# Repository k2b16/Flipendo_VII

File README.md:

Step 4: Setting up Component Library

Note: If done according to the guide, the component library will be located in the Component_library folder.

To set up the component library, you first have to open KiCAD. Then in the upper menu bar, open Preferences -> Configure Paths... In there first press the + to add a new entry.

As the next step, open Preferences -> Manage Symbol Libraries... There, Press the button shown on the image below, marked by 1 and then in the folder selection window, select all of the files inside Component Library/Symbols directory.

After that, bunch of symbol entries should appear to the symbol library browser.

A very similar thing has to be done with Footprints, except instead of selecting files inside the Footprints directory you must choose all of the .pretty directories in there. Adding Footprint libraries is done in Preferences -> Manage Footprint Libraries...

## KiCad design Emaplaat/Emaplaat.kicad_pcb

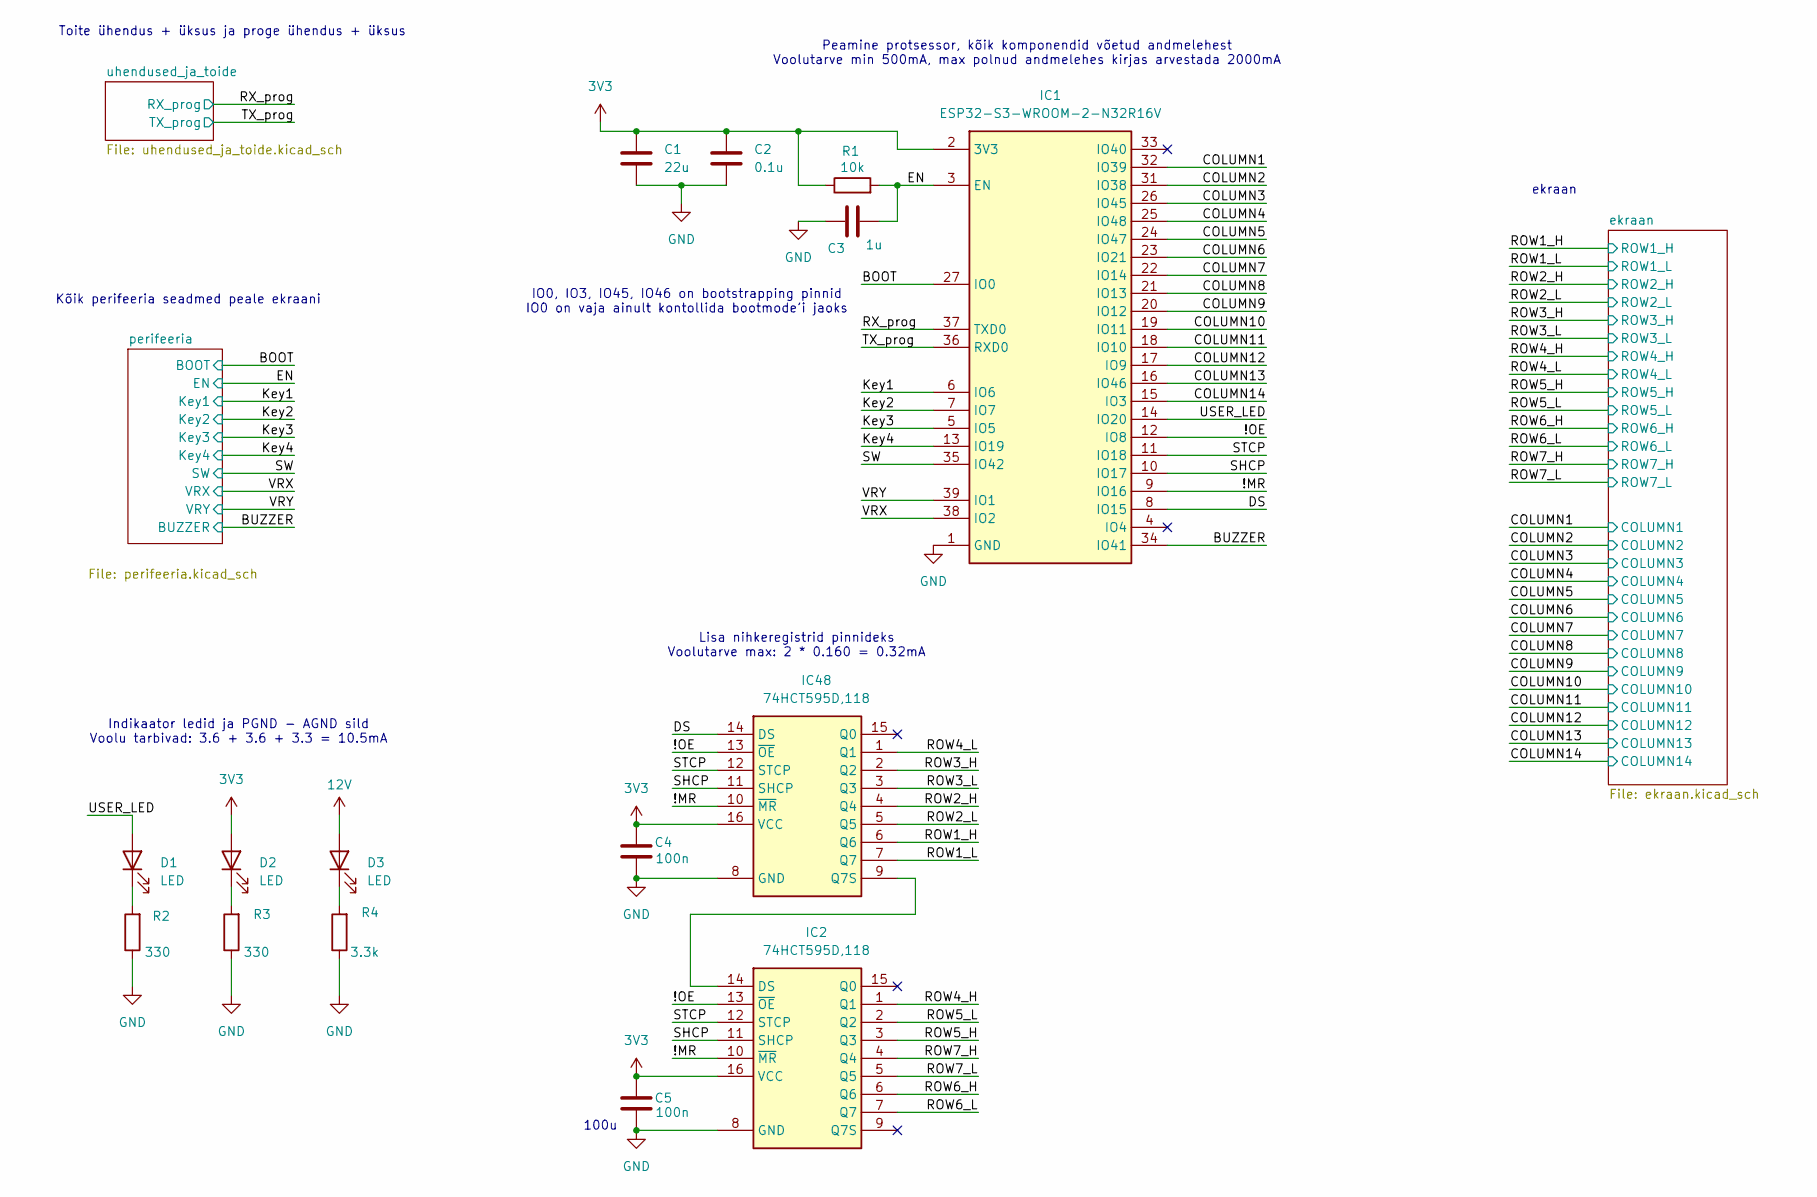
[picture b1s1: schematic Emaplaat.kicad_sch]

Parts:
C1: 22u; C_1206_3216Metric_Pad1.33x1.80mm_HandSolder
C2: 0.1u; C_0603_1608Metric_Pad1.08x0.95mm_HandSolder
C3: 1u; C_0603_1608Metric_Pad1.08x0.95mm_HandSolder
C4, C5: 100n; C_0603_1608Metric_Pad1.08x0.95mm_HandSolder
D1, D2, D3: LED; LED_0603_1608Metric_Pad1.05x0.95mm_HandSolder
IC1: ESP32-S3-WROOM-2-N32R16V; ESP32S3WROOM2N32R16V; Mouser Part Number 356-SP32S3WM2N32R16V
IC2, IC48: 74HCT595D,118; SOIC127P600X175-16N; Manufacturer_Part_Number 74HCT595D,118
R1: 10k; R_0603_1608Metric_Pad0.98x0.95mm_HandSolder
R2, R3: 330; R_0603_1608Metric_Pad0.98x0.95mm_HandSolder
R4: 3.3k; R_0603_1608Metric_Pad0.98x0.95mm_HandSolder

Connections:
3V3: C1.1, C2.1, C4.2, C5.2, D2.2 (A), IC1.2 (3V3), IC2.16 (VCC), IC48.16 (VCC), R1.1; also elsewhere on the board
12V: D3.2 (A); also elsewhere on the board
/!MR: IC1.9 (IO16), IC2.10 (~MR), IC48.10 (~MR)
/!OE: IC1.12 (IO8), IC2.13 (~OE), IC48.13 (~OE)
/BOOT: IC1.27 (IO0); also elsewhere on the board
/BUZZER: IC1.34 (IO41); also elsewhere on the board
/COLUMN1: IC1.32 (IO39); also elsewhere on the board
/COLUMN2: IC1.31 (IO38); also elsewhere on the board
/COLUMN3: IC1.26 (IO45); also elsewhere on the board
/COLUMN4: IC1.25 (IO48); also elsewhere on the board
/COLUMN5: IC1.24 (IO47); also elsewhere on the board
/COLUMN6: IC1.23 (IO21); also elsewhere on the board
/COLUMN7: IC1.22 (IO14); also elsewhere on the board
/COLUMN8: IC1.21 (IO13); also elsewhere on the board
/COLUMN9: IC1.20 (IO12); also elsewhere on the board
/COLUMN10: IC1.19 (IO11); also elsewhere on the board
/COLUMN11: IC1.18 (IO10); also elsewhere on the board
/COLUMN12: IC1.17 (IO9); also elsewhere on the board
/COLUMN13: IC1.16 (IO46); also elsewhere on the board
/COLUMN14: IC1.15 (IO3); also elsewhere on the board
/DS: IC1.8 (IO15), IC48.14 (DS)
/EN: C3.2, IC1.3 (EN), R1.2; also elsewhere on the board
/Key1: IC1.6 (IO6); also elsewhere on the board
/Key2: IC1.7 (IO7); also elsewhere on the board
/Key3: IC1.5 (IO5); also elsewhere on the board
/Key4: IC1.13 (IO19); also elsewhere on the board
/ROW1_H: IC48.6 (Q6); also elsewhere on the board
/ROW1_L: IC48.7 (Q7); also elsewhere on the board
/ROW2_H: IC48.4 (Q4); also elsewhere on the board
/ROW2_L: IC48.5 (Q5); also elsewhere on the board
/ROW3_H: IC48.2 (Q2); also elsewhere on the board
/ROW3_L: IC48.3 (Q3); also elsewhere on the board
/ROW4_H: IC2.1 (Q1); also elsewhere on the board
/ROW4_L: IC48.1 (Q1); also elsewhere on the board
/ROW5_H: IC2.3 (Q3); also elsewhere on the board
/ROW5_L: IC2.2 (Q2); also elsewhere on the board
/ROW6_H: IC2.6 (Q6); also elsewhere on the board
/ROW6_L: IC2.7 (Q7); also elsewhere on the board
/ROW7_H: IC2.4 (Q4); also elsewhere on the board
/ROW7_L: IC2.5 (Q5); also elsewhere on the board
/RX_prog: IC1.37 (TXD0); also elsewhere on the board
/SHCP: IC1.10 (IO17), IC2.11 (SHCP), IC48.11 (SHCP)
/STCP: IC1.11 (IO18), IC2.12 (STCP), IC48.12 (STCP)
/SW: IC1.35 (IO42); also elsewhere on the board
/TX_prog: IC1.36 (RXD0); also elsewhere on the board
/USER_LED: D1.2 (A), IC1.14 (IO20)
/VRX: IC1.38 (IO2); also elsewhere on the board
/VRY: IC1.39 (IO1); also elsewhere on the board
GND: C1.2, C2.2, C3.1, C4.1, C5.1, IC1.1 (GND), IC1.40 (GND), IC1.41 (GND), IC1.42 (GND), IC1.43 (GND), IC1.44 (GND), IC1.45 (GND), IC1.46 (GND), IC1.47 (GND), IC1.48 (GND), IC1.49 (GND), IC2.8 (GND), IC48.8 (GND), R2.1, R3.1, R4.1; also elsewhere on the board
unnamed: D1.1 (K), R2.2
unnamed: D2.1 (K), R3.2
unnamed: D3.1 (K), R4.2
unnamed: IC2.14 (DS), IC48.9 (Q7S)

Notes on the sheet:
Toite ühendus + üksus ja proge ühendus + üksus
Kõik perifeeria seadmed peale ekraani
Indikaator ledid ja PGND - AGND sild Voolu tarbivad: 3.6 + 3.6 + 3.3 = 10.5mA
Peamine protsessor, kõik komponendid võetud andmelehest Voolutarve min 500mA, max polnud andmelehes kirjas arvestada 2000mA
IO0, IO3, IO45, IO46 on bootstrapping pinnid IO0 on vaja ainult kontollida bootmode'i jaoks
ekraan
Lisa nihkeregistrid pinnideks Voolutarve max: 2 * 0.160 = 0.32mA
100u

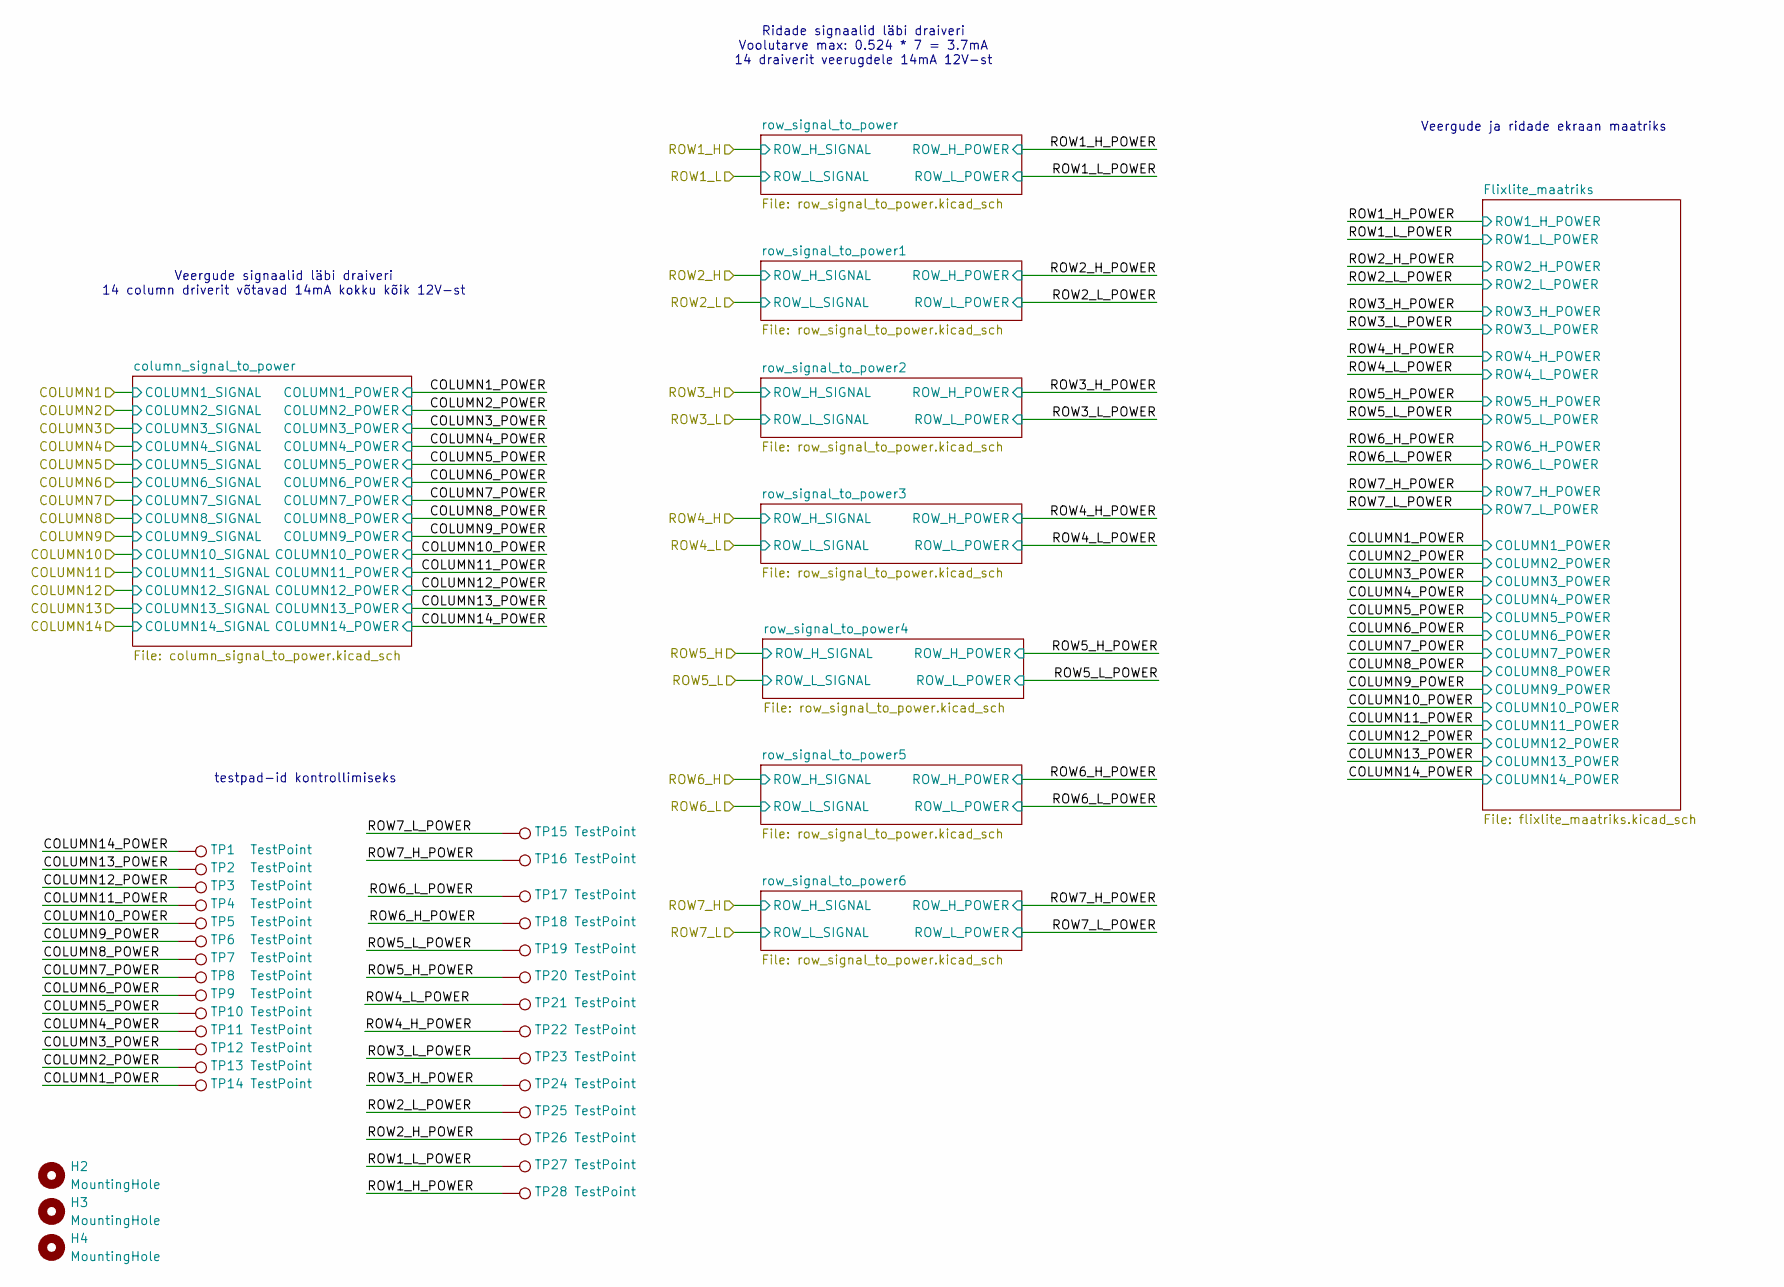
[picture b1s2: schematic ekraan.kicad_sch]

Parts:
H2, H3, H4: MountingHole; MountingHole_3mm_Pad
TP1, TP2, TP3, TP4, TP5, TP6, TP7, TP8, TP9, TP10, TP11, TP12, TP13, TP14, TP15, TP16, TP17, TP18, TP19, TP20, TP21, TP22, TP23, TP24, TP25, TP26, TP27, TP28: TestPoint; TestPoint_Pad_D1.0mm

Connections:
/ekraan/COLUMN1_POWER: TP14.1; also elsewhere on the board
/ekraan/COLUMN2_POWER: TP13.1; also elsewhere on the board
/ekraan/COLUMN3_POWER: TP12.1; also elsewhere on the board
/ekraan/COLUMN4_POWER: TP11.1; also elsewhere on the board
/ekraan/COLUMN5_POWER: TP10.1; also elsewhere on the board
/ekraan/COLUMN6_POWER: TP9.1; also elsewhere on the board
/ekraan/COLUMN7_POWER: TP8.1; also elsewhere on the board
/ekraan/COLUMN8_POWER: TP7.1; also elsewhere on the board
/ekraan/COLUMN9_POWER: TP6.1; also elsewhere on the board
/ekraan/COLUMN10_POWER: TP5.1; also elsewhere on the board
/ekraan/COLUMN11_POWER: TP4.1; also elsewhere on the board
/ekraan/COLUMN12_POWER: TP3.1; also elsewhere on the board
/ekraan/COLUMN13_POWER: TP2.1; also elsewhere on the board
/ekraan/COLUMN14_POWER: TP1.1; also elsewhere on the board
/ekraan/ROW1_H_POWER: TP28.1; also elsewhere on the board
/ekraan/ROW1_L_POWER: TP27.1; also elsewhere on the board
/ekraan/ROW2_H_POWER: TP26.1; also elsewhere on the board
/ekraan/ROW2_L_POWER: TP25.1; also elsewhere on the board
/ekraan/ROW3_H_POWER: TP24.1; also elsewhere on the board
/ekraan/ROW3_L_POWER: TP23.1; also elsewhere on the board
/ekraan/ROW4_H_POWER: TP22.1; also elsewhere on the board
/ekraan/ROW4_L_POWER: TP21.1; also elsewhere on the board
/ekraan/ROW5_H_POWER: TP20.1; also elsewhere on the board
/ekraan/ROW5_L_POWER: TP19.1; also elsewhere on the board
/ekraan/ROW6_H_POWER: TP18.1; also elsewhere on the board
/ekraan/ROW6_L_POWER: TP17.1; also elsewhere on the board
/ekraan/ROW7_H_POWER: TP16.1; also elsewhere on the board
/ekraan/ROW7_L_POWER: TP15.1; also elsewhere on the board

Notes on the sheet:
Veergude ja ridade ekraan maatriks
Veergude signaalid läbi draiveri 14 column driverit võtavad 14mA kokku kõik 12V-st
Ridade signaalid läbi draiveri Voolutarve max: 0.524 * 7 = 3.7mA 14 draiverit veerugdele 14mA 12V-st
testpad-id kontrollimiseks

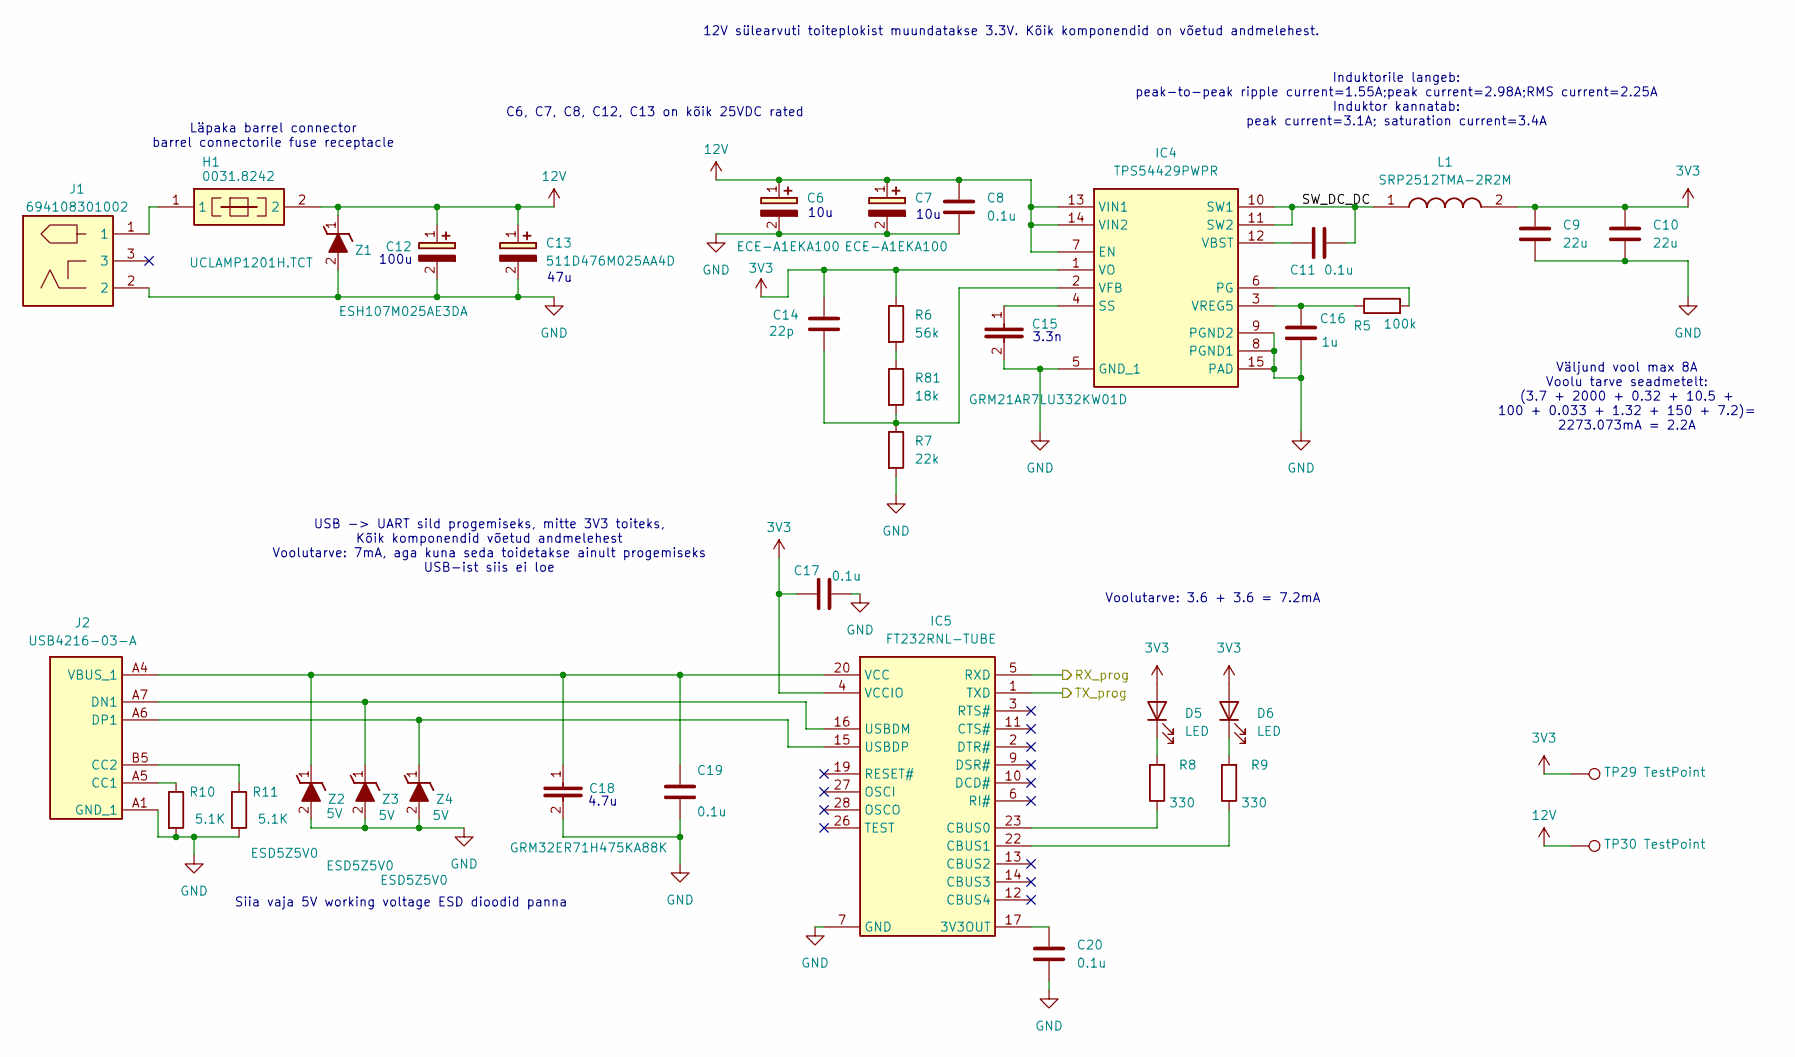
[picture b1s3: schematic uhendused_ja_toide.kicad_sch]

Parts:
C6, C7: ECE-A1EKA100; CAPPRD150W50D400H800; Mouser Part Number 667-ECE-A1EKA100
C8, C11, C17, C19, C20: 0.1u; C_0603_1608Metric_Pad1.08x0.95mm_HandSolder
C9, C10: 22u; C_1206_3216Metric_Pad1.33x1.80mm_HandSolder
C12: ESH107M025AE3DA; CAPPRD250W50D630H1250; Mouser Part Number 80-ESH107M025AE3DA
C13: 511D476M025AA4D; Mouser Part Number 75-511D476M025AA4D
C14: 22p; C_0603_1608Metric_Pad1.08x0.95mm_HandSolder
C15: GRM21AR7LU332KW01D; CAPC2012X130N; Manufacturer_Part_Number GRM21AR7LU332KW01D
C16: 1u; C_0603_1608Metric_Pad1.08x0.95mm_HandSolder
C18: GRM32ER71H475KA88K; CAPC3225X270N; Mouser Part Number 81-GRM32ER71H475KA8K
D5, D6: LED; LED_0603_1608Metric_Pad1.05x0.95mm_HandSolder
H1: 0031.8242; 00318242; Mouser Part Number N/A
IC4: TPS54429PWPR; Texas_HTSSOP-14-1EP_4.4x5mm_P0.65mm_EP3.4x5mm_Mask3.155x3.2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; Mouser Part Number 595-TPS54429PWPR
IC5: FT232RNL-TUBE; SOP65P780X200-28N; Mouser Part Number 895-FT232RNL-TUBE
J1: 694108301002; Manufacturer_Part_Number 694108301002
J2: USB4216-03-A; USB421603A; Manufacturer_Part_Number USB4216-03-A
L1: SRP2512TMA-2R2M; SRP2512TMA2R2M; Mouser Part Number 652-SRP2512TMA-2R2M
R5: 100k; R_0603_1608Metric_Pad0.98x0.95mm_HandSolder
R6: 56k; R_0603_1608Metric_Pad0.98x0.95mm_HandSolder
R7: 22k; R_0603_1608Metric_Pad0.98x0.95mm_HandSolder
R8, R9: 330; R_0603_1608Metric_Pad0.98x0.95mm_HandSolder
R10, R11: 5.1K; R_0603_1608Metric_Pad0.98x0.95mm_HandSolder
R81: 18k; R_0603_1608Metric_Pad0.98x0.95mm_HandSolder
TP29, TP30: TestPoint; TestPoint_Pad_D1.0mm
Z1: UCLAMP1201H.TCT; SODFL1608X70N; Mouser Part Number 947-UCLAMP1201H.TCT
Z2, Z3, Z4: ESD5Z5V0; D_SOD-523; Working voltage 5V

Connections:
3V3: C9.1, C10.1, C14.1, C17.1, D5.2 (A), D6.2 (A), IC4.1 (VO), IC5.4 (VCCIO), L1.2, R6.1, TP29.1; also elsewhere on the board
12V: C6.1 (+), C7.1 (+), C8.1, C12.1 (+), C13.1 (+), H1.2, IC4.7 (EN), IC4.13 (VIN1), IC4.14 (VIN2), TP30.1, Z1.1 (K); also elsewhere on the board
/RX_prog: IC5.5 (RXD); also elsewhere on the board
/TX_prog: IC5.1 (TXD); also elsewhere on the board
/uhendused_ja_toide/SW_DC_DC: C11.2, IC4.10 (SW1), IC4.11 (SW2), L1.1
GND: C6.2 (-), C7.2 (-), C8.2, C9.2, C10.2, C12.2 (-), C13.2 (-), C15.2, C16.2, C17.2, C18.2, C19.2, C20.2, IC4.5 (GND_1), IC4.8 (PGND1), IC4.9 (PGND2), IC4.15 (PAD), IC5.7 (GND), IC5.18 (GND_2), IC5.21 (GND_3), IC5.25 (AGND), J1.2, J2.A1 (GND_1), J2.B1 (GND_2), J2.G1 (GND_3), J2.G2 (GND_4), J2.G3 (GND_5), J2.G4 (GND_6), R7.2, R10.2, R11.2, Z1.2 (A), Z2.2 (A), Z3.2 (A), Z4.2 (A); also elsewhere on the board
unnamed: D5.1 (K), R8.2
unnamed: D6.1 (K), R9.2
unnamed: H1.1, J1.1
unnamed: IC4.6 (PG), R5.2
unnamed: C15.1, IC4.4 (SS)
unnamed: C11.1, IC4.12 (VBST)
unnamed: C14.2, IC4.2 (VFB), R7.1, R81.2
unnamed: C16.1, IC4.3 (VREG5), R5.1
unnamed: C20.1, IC5.17 (3V3OUT)
unnamed: IC5.23 (CBUS0), R8.1
unnamed: IC5.22 (CBUS1), R9.1
unnamed: IC5.16 (USBDM), J2.A7 (DN1), J2.B7 (DN2), Z3.1 (K)
unnamed: IC5.15 (USBDP), J2.A6 (DP1), J2.B6 (DP2), Z4.1 (K)
unnamed: C18.1, C19.1, IC5.20 (VCC), J2.A4 (VBUS_1), J2.B4 (VBUS_2), Z2.1 (K)
unnamed: J2.A5 (CC1), R10.1
unnamed: J2.B5 (CC2), R11.1
unnamed: J2.A8 (SBU1), J2.B8 (SBU2)
unnamed: R6.2, R81.1

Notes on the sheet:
12V sülearvuti toiteplokist muundatakse 3.3V. Kõik komponendid on võetud andmelehest.
C6, C7, C8, C12, C13 on kõik 25VDC rated
47u
10u
Siia vaja 5V working voltage ESD dioodid panna
Väljund vool max 8A Voolu tarve seadmetelt: (3.7 + 2000 + 0.32 + 10.5 + 100 + 0.033 + 1.32 + 150 + 7.2)= 2273.073mA = 2.2A
USB -> UART sild progemiseks, mitte 3V3 toiteks, Kõik komponendid võetud andmelehest Voolutarve: 7mA, aga kuna seda toidetakse ainult progemiseks USB-ist siis ei loe
4.7u
100u
Induktorile langeb: peak-to-peak ripple current=1.55A;peak current=2.98A;RMS current=2.25A Induktor kannatab: peak current=3.1A; saturation current=3.4A
3.3n
Läpaka barrel connector barrel connectorile fuse receptacle
Voolutarve: 3.6 + 3.6 = 7.2mA

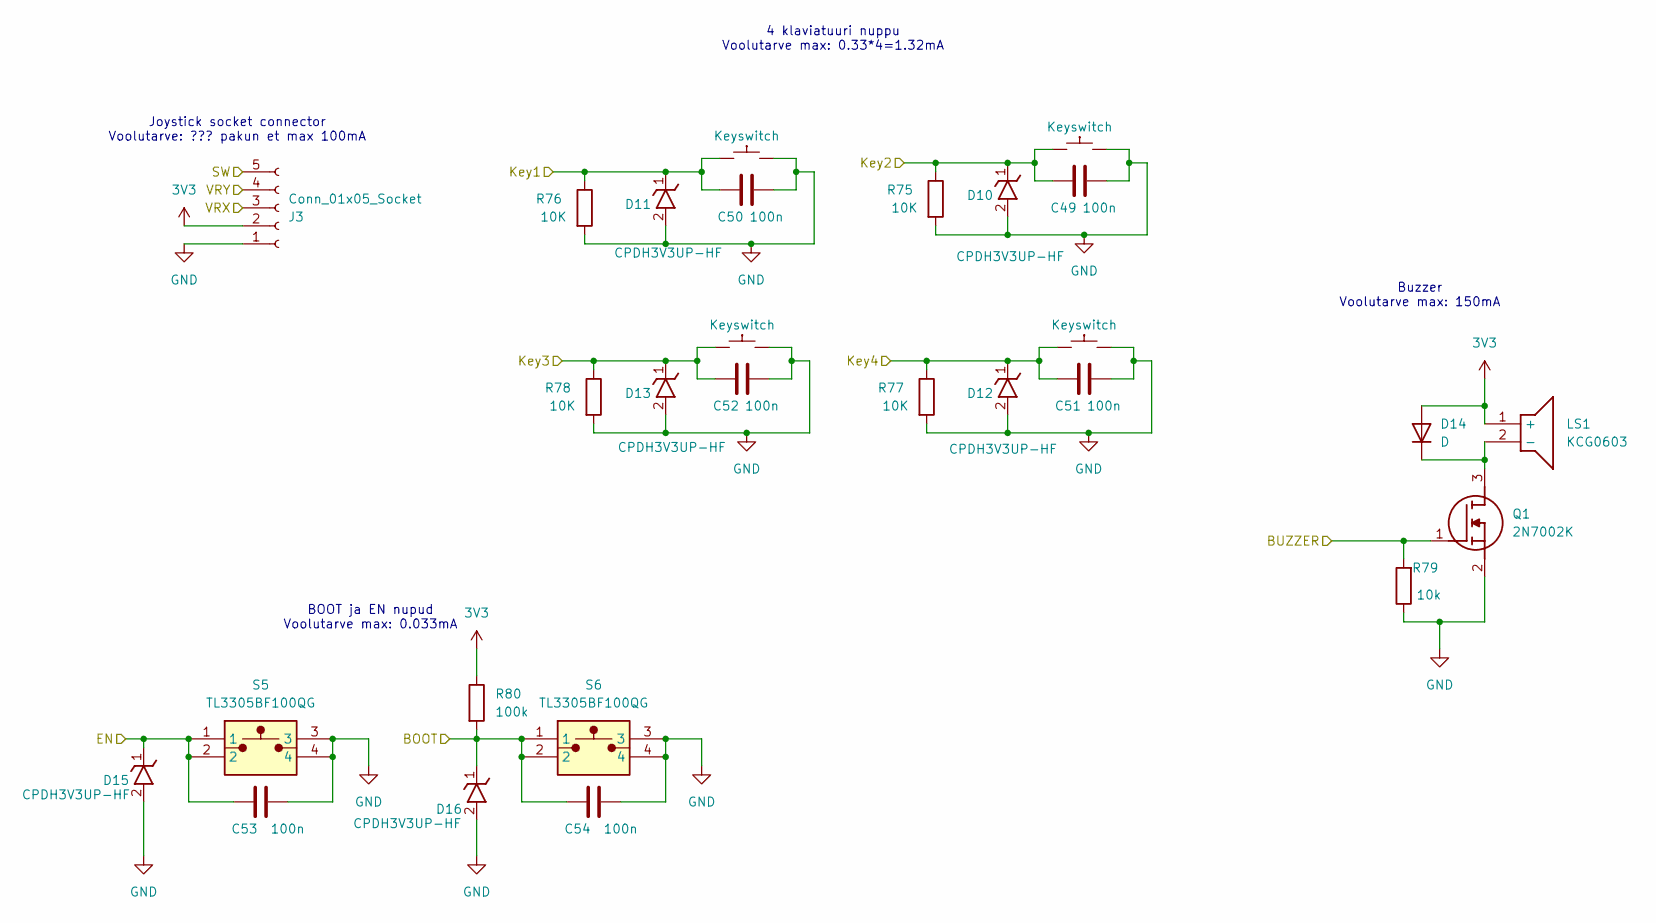
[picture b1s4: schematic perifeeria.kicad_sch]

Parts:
C49, C50, C51, C52, C53, C54: 100n; C_0603_1608Metric_Pad1.08x0.95mm_HandSolder
D10, D11, D12, D13, D15, D16: CPDH3V3UP-HF; D_SOD-523; Mouser Part Number 750-CPDH3V3UP-HF
D14: D; SOD-123FL
J3: Conn_01x05_Socket; PinSocket_1x05_P2.54mm_Horizontal
LS1: KCG0603; Manufacturer_Part_Number KCG0603
Q1: 2N7002K; SOT95P240X120-3N; Mouser Part Number 512-2N7002K
R75, R76, R77, R78: 10K; R_0603_1608Metric_Pad0.98x0.95mm_HandSolder
R79: 10k; R_0603_1608Metric_Pad0.98x0.95mm_HandSolder
R80: 100k; R_0603_1608Metric_Pad0.98x0.95mm_HandSolder
S1, S2, S3, S4: Keyswitch; SW_Cherry_MX_1.00u_PCB
S5, S6: TL3305BF100QG; TL3305BF160QG; Mouser Part Number 612-TL3305BF100QG

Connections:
3V3: D14.2 (A), J3.2, LS1.1 (+), R80.1; also elsewhere on the board
/BOOT: C54.1, D16.1 (K), R80.2, S6.1, S6.2; also elsewhere on the board
/BUZZER: Q1.1 (G), R79.2; also elsewhere on the board
/EN: C53.1, D15.1 (K), S5.1, S5.2; also elsewhere on the board
/Key1: C50.1, D11.1 (K), R76.1, S2.1; also elsewhere on the board
/Key2: C49.1, D10.1 (K), R75.1, S1.1; also elsewhere on the board
/Key3: C52.1, D13.1 (K), R78.1, S4.1; also elsewhere on the board
/Key4: C51.1, D12.1 (K), R77.1, S3.1; also elsewhere on the board
/SW: J3.5; also elsewhere on the board
/VRX: J3.3; also elsewhere on the board
/VRY: J3.4; also elsewhere on the board
GND: C49.2, C50.2, C51.2, C52.2, C53.2, C54.2, D10.2 (A), D11.2 (A), D12.2 (A), D13.2 (A), D15.2 (A), D16.2 (A), J3.1, Q1.2 (S), R75.2, R76.2, R77.2, R78.2, R79.1, S1.2, S2.2, S3.2, S4.2, S5.3, S5.4, S6.3, S6.4; also elsewhere on the board
unnamed: D14.1 (K), LS1.2 (-), Q1.3 (D)

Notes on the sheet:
Buzzer Voolutarve max: 150mA
4 klaviatuuri nuppu Voolutarve max: 0.33*4=1.32mA
Joystick socket connector Voolutarve: ??? pakun et max 100mA
BOOT ja EN nupud Voolutarve max: 0.033mA

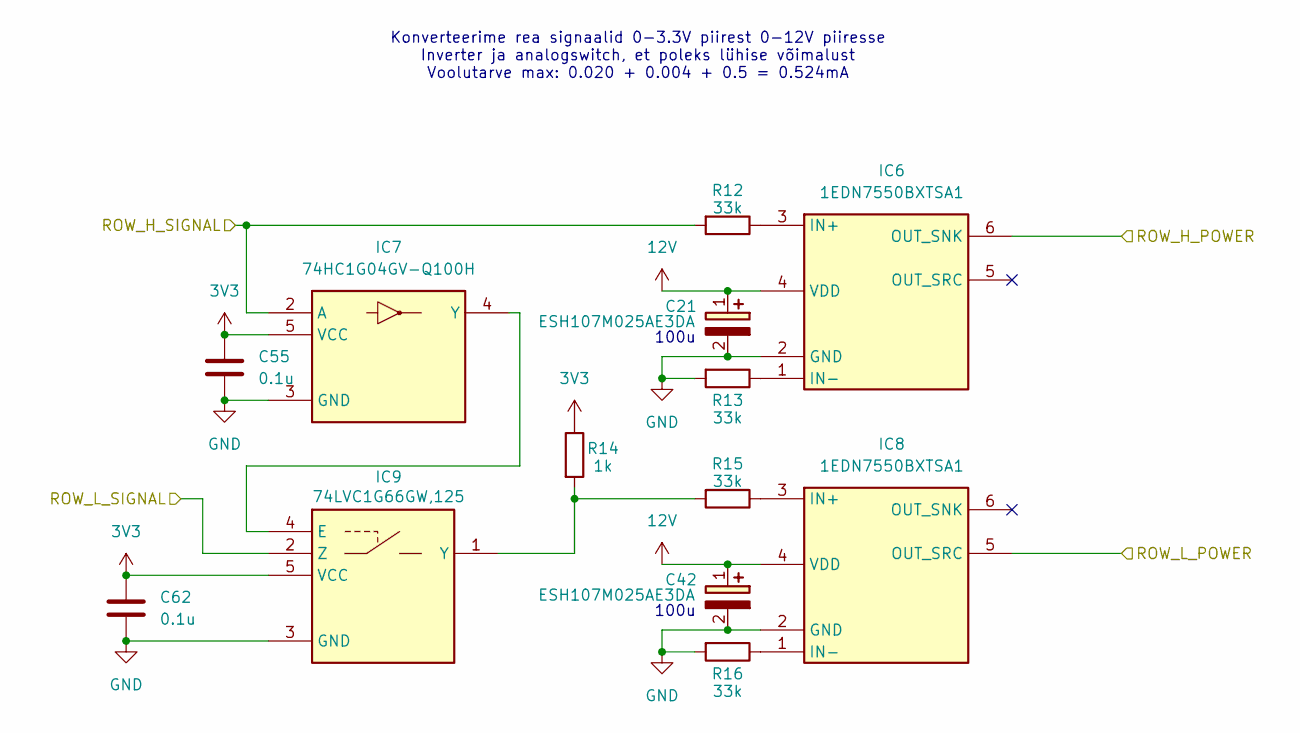
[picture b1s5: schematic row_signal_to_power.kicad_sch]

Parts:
C21, C42: ESH107M025AE3DA; CAPPRD250W50D630H1250; Mouser Part Number 80-ESH107M025AE3DA
C55, C62: 0.1u; C_0603_1608Metric_Pad1.08x0.95mm_HandSolder
IC6, IC8: 1EDN7550BXTSA1; SOT95P280X145-6N; Mouser Part Number 726-1EDN7550BXTSA1
IC7: 74HC1G04GV-Q100H; SOT95P275X110-5N; Mouser Part Number 771-74HC1G04GV-Q100H
IC9: 74LVC1G66GW,125; SOT65P212X110-5N; Mouser Part Number 771-74LVC1G66GW-G
R12, R13, R15, R16: 33k; R_0603_1608Metric_Pad0.98x0.95mm_HandSolder
R14: 1k; R_0603_1608Metric_Pad0.98x0.95mm_HandSolder

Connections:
3V3: C55.1, C62.1, IC7.5 (VCC), IC9.5 (VCC), R14.1; also elsewhere on the board
12V: C21.1 (+), C42.1 (+), IC6.4 (VDD), IC8.4 (VDD); also elsewhere on the board
/ROW2_H: IC7.2 (A), R12.2; also elsewhere on the board
/ROW2_L: IC9.2 (Z); also elsewhere on the board
/ekraan/ROW2_H_POWER: IC6.6 (OUT_SNK); also elsewhere on the board
/ekraan/ROW2_L_POWER: IC8.5 (OUT_SRC); also elsewhere on the board
GND: C21.2 (-), C42.2 (-), C55.2, C62.2, IC6.2 (GND), IC7.3 (GND), IC8.2 (GND), IC9.3 (GND), R13.2, R16.2; also elsewhere on the board
unnamed: IC6.3 (IN+), R12.1
unnamed: IC6.1 (IN-), R13.1
unnamed: IC7.4 (Y), IC9.4 (E)
unnamed: IC8.3 (IN+), R15.1
unnamed: IC8.1 (IN-), R16.1
unnamed: IC9.1 (Y), R14.2, R15.2

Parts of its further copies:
C22, C23, C24, C25, C26, C41, C43, C44, C45, C46, C47, C48: ESH107M025AE3DA; CAPPRD250W50D630H1250; Mouser Part Number 80-ESH107M025AE3DA
C56, C57, C58, C59, C60, C61, C63, C64, C65, C66, C67, C68: 0.1u; C_0603_1608Metric_Pad1.08x0.95mm_HandSolder
IC10, IC12, IC14, IC16, IC32, IC34, IC36, IC38, IC40, IC42, IC44, IC46: 1EDN7550BXTSA1; SOT95P280X145-6N; Mouser Part Number 726-1EDN7550BXTSA1
IC11, IC15, IC33, IC37, IC41, IC45: 74HC1G04GV-Q100H; SOT95P275X110-5N; Mouser Part Number 771-74HC1G04GV-Q100H
IC13, IC17, IC35, IC39, IC43, IC47: 74LVC1G66GW,125; SOT65P212X110-5N; Mouser Part Number 771-74LVC1G66GW-G
R17, R18, R20, R21, R22, R23, R25, R26, R55, R56, R58, R59, R60, R61, R63, R64, R65, R66, R68, R69, R70, R71, R73, R74: 33k; R_0603_1608Metric_Pad0.98x0.95mm_HandSolder
R19, R24, R57, R62, R67, R72: 1k; R_0603_1608Metric_Pad0.98x0.95mm_HandSolder

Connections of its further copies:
3V3: C56.1, C57.1, C58.1, C59.1, C60.1, C61.1, C63.1, C64.1, C65.1, C66.1, C67.1, C68.1, IC11.5 (VCC), IC13.5 (VCC), IC15.5 (VCC), IC17.5 (VCC), IC33.5 (VCC), IC35.5 (VCC), IC37.5 (VCC), IC39.5 (VCC), IC41.5 (VCC), IC43.5 (VCC), IC45.5 (VCC), IC47.5 (VCC), R19.1, R24.1, R57.1, R62.1, R67.1, R72.1; also elsewhere on the board
12V: C22.1 (+), C23.1 (+), C24.1 (+), C25.1 (+), C26.1 (+), C41.1 (+), C43.1 (+), C44.1 (+), C45.1 (+), C46.1 (+), C47.1 (+), C48.1 (+), IC10.4 (VDD), IC12.4 (VDD), IC14.4 (VDD), IC16.4 (VDD), IC32.4 (VDD), IC34.4 (VDD), IC36.4 (VDD), IC38.4 (VDD), IC40.4 (VDD), IC42.4 (VDD), IC44.4 (VDD), IC46.4 (VDD); also elsewhere on the board
/ROW1_H: IC15.2 (A), R22.2; also elsewhere on the board
/ROW1_L: IC17.2 (Z); also elsewhere on the board
/ROW3_H: IC11.2 (A), R17.2; also elsewhere on the board
/ROW3_L: IC13.2 (Z); also elsewhere on the board
/ROW4_H: IC33.2 (A), R55.2; also elsewhere on the board
/ROW4_L: IC35.2 (Z); also elsewhere on the board
/ROW5_H: IC37.2 (A), R60.2; also elsewhere on the board
/ROW5_L: IC39.2 (Z); also elsewhere on the board
/ROW6_H: IC41.2 (A), R65.2; also elsewhere on the board
/ROW6_L: IC43.2 (Z); also elsewhere on the board
/ROW7_H: IC45.2 (A), R70.2; also elsewhere on the board
/ROW7_L: IC47.2 (Z); also elsewhere on the board
/ekraan/ROW1_H_POWER: IC14.6 (OUT_SNK); also elsewhere on the board
/ekraan/ROW1_L_POWER: IC16.5 (OUT_SRC); also elsewhere on the board
/ekraan/ROW3_H_POWER: IC10.6 (OUT_SNK); also elsewhere on the board
/ekraan/ROW3_L_POWER: IC12.5 (OUT_SRC); also elsewhere on the board
/ekraan/ROW4_H_POWER: IC32.6 (OUT_SNK); also elsewhere on the board
/ekraan/ROW4_L_POWER: IC34.5 (OUT_SRC); also elsewhere on the board
/ekraan/ROW5_H_POWER: IC36.6 (OUT_SNK); also elsewhere on the board
/ekraan/ROW5_L_POWER: IC38.5 (OUT_SRC); also elsewhere on the board
/ekraan/ROW6_H_POWER: IC40.6 (OUT_SNK); also elsewhere on the board
/ekraan/ROW6_L_POWER: IC42.5 (OUT_SRC); also elsewhere on the board
/ekraan/ROW7_H_POWER: IC44.6 (OUT_SNK); also elsewhere on the board
/ekraan/ROW7_L_POWER: IC46.5 (OUT_SRC); also elsewhere on the board
GND: C22.2 (-), C23.2 (-), C24.2 (-), C25.2 (-), C26.2 (-), C41.2 (-), C43.2 (-), C44.2 (-), C45.2 (-), C46.2 (-), C47.2 (-), C48.2 (-), C56.2, C57.2, C58.2, C59.2, C60.2, C61.2, C63.2, C64.2, C65.2, C66.2, C67.2, C68.2, IC10.2 (GND), IC11.3 (GND), IC12.2 (GND), IC13.3 (GND), IC14.2 (GND), IC15.3 (GND), IC16.2 (GND), IC17.3 (GND), IC32.2 (GND), IC33.3 (GND), IC34.2 (GND), IC35.3 (GND), IC36.2 (GND), IC37.3 (GND), IC38.2 (GND), IC39.3 (GND), IC40.2 (GND), IC41.3 (GND), IC42.2 (GND), IC43.3 (GND), IC44.2 (GND), IC45.3 (GND), IC46.2 (GND), IC47.3 (GND), R18.2, R21.2, R23.2, R26.2, R56.2, R59.2, R61.2, R64.2, R66.2, R69.2, R71.2, R74.2; also elsewhere on the board
unnamed: IC10.3 (IN+), R17.1
unnamed: IC10.1 (IN-), R18.1
unnamed: IC11.4 (Y), IC13.4 (E)
unnamed: IC12.3 (IN+), R20.1
unnamed: IC12.1 (IN-), R21.1
unnamed: IC13.1 (Y), R19.2, R20.2
unnamed: IC14.3 (IN+), R22.1
unnamed: IC14.1 (IN-), R23.1
unnamed: IC15.4 (Y), IC17.4 (E)
unnamed: IC16.3 (IN+), R25.1
unnamed: IC16.1 (IN-), R26.1
unnamed: IC17.1 (Y), R24.2, R25.2
unnamed: IC32.3 (IN+), R55.1
unnamed: IC32.1 (IN-), R56.1
unnamed: IC33.4 (Y), IC35.4 (E)
unnamed: IC34.3 (IN+), R58.1
unnamed: IC34.1 (IN-), R59.1
unnamed: IC35.1 (Y), R57.2, R58.2
unnamed: IC36.3 (IN+), R60.1
unnamed: IC36.1 (IN-), R61.1
unnamed: IC37.4 (Y), IC39.4 (E)
unnamed: IC38.3 (IN+), R63.1
unnamed: IC38.1 (IN-), R64.1
unnamed: IC39.1 (Y), R62.2, R63.2
unnamed: IC40.3 (IN+), R65.1
unnamed: IC40.1 (IN-), R66.1
unnamed: IC41.4 (Y), IC43.4 (E)
unnamed: IC42.3 (IN+), R68.1
unnamed: IC42.1 (IN-), R69.1
unnamed: IC43.1 (Y), R67.2, R68.2
unnamed: IC44.3 (IN+), R70.1
unnamed: IC44.1 (IN-), R71.1
unnamed: IC45.4 (Y), IC47.4 (E)
unnamed: IC46.3 (IN+), R73.1
unnamed: IC46.1 (IN-), R74.1
unnamed: IC47.1 (Y), R72.2, R73.2

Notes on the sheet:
Konverteerime rea signaalid 0-3.3V piirest 0-12V piiresse Inverter ja analogswitch, et poleks lühise võimalust Voolutarve max: 0.020 + 0.004 + 0.5 = 0.524mA
100u
